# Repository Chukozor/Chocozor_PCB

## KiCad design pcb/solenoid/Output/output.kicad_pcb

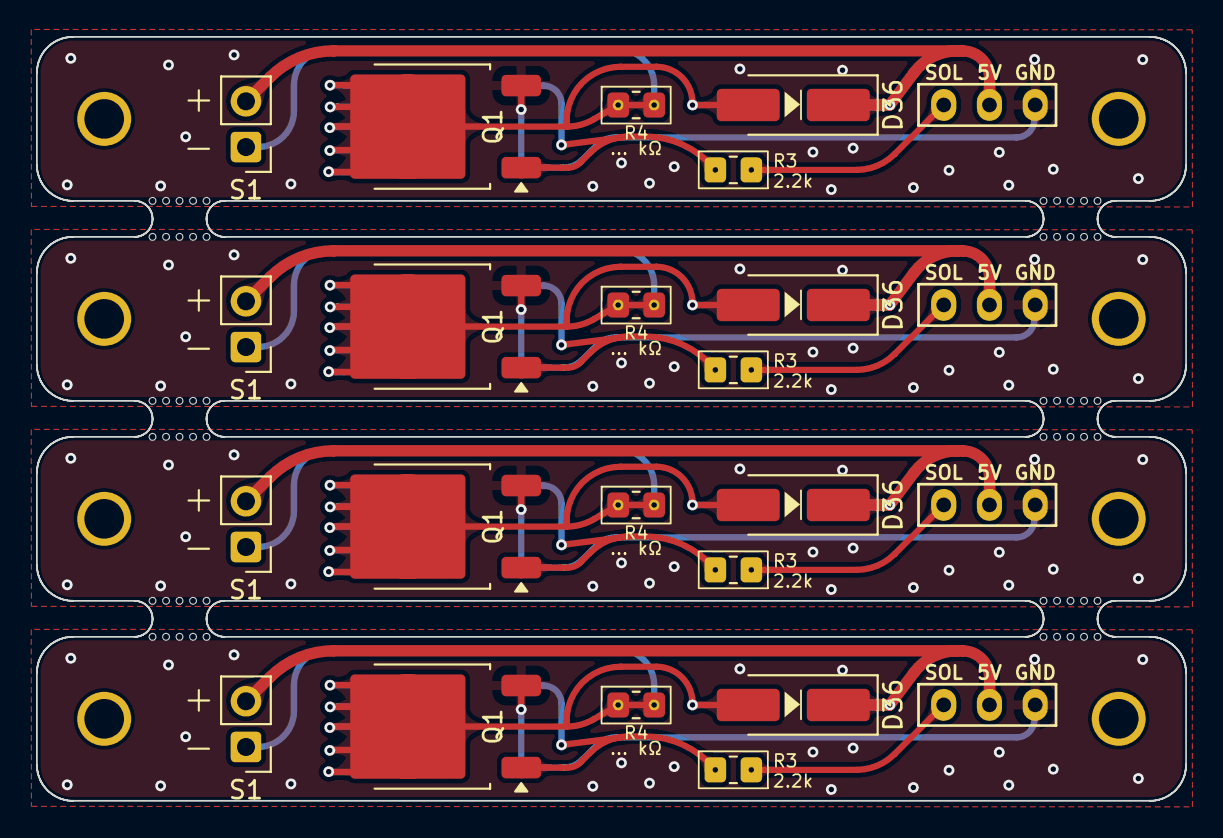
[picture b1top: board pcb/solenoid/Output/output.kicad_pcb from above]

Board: 2 copper layers, 63.8 x 42.4 mm, 92 parts (0 on the bottom side), 20 nets.

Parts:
D36, D36#2, D36#3, D36#4: SS14 (or M1) package SMA; D_SMA_Handsoldering-Chuk
J3, J3#2, J3#3, J3#4: Conn_01x03; solenoid_ribon_connector
KiKit_MB_1_1, KiKit_MB_1_2, KiKit_MB_1_3, KiKit_MB_1_4, KiKit_MB_1_5, KiKit_MB_2_1, KiKit_MB_2_2, KiKit_MB_2_3, KiKit_MB_2_4, KiKit_MB_2_5, KiKit_MB_3_1, KiKit_MB_3_2, KiKit_MB_3_3, KiKit_MB_3_4, KiKit_MB_3_5, KiKit_MB_4_1, KiKit_MB_4_2, KiKit_MB_4_3, KiKit_MB_4_4, KiKit_MB_4_5, KiKit_MB_5_1, KiKit_MB_5_2, KiKit_MB_5_3, KiKit_MB_5_4, KiKit_MB_5_5, KiKit_MB_6_1, KiKit_MB_6_2, KiKit_MB_6_3, KiKit_MB_6_4, KiKit_MB_6_5, KiKit_MB_7_1, KiKit_MB_7_2, KiKit_MB_7_3, KiKit_MB_7_4, KiKit_MB_7_5, KiKit_MB_8_1, KiKit_MB_8_2, KiKit_MB_8_3, KiKit_MB_8_4, KiKit_MB_8_5, KiKit_MB_9_1, KiKit_MB_9_2, KiKit_MB_9_3, KiKit_MB_9_4, KiKit_MB_9_5, KiKit_MB_10_1, KiKit_MB_10_2, KiKit_MB_10_3, KiKit_MB_10_4, KiKit_MB_10_5, KiKit_MB_11_1, KiKit_MB_11_2, KiKit_MB_11_3, KiKit_MB_11_4, KiKit_MB_11_5, KiKit_MB_12_1, KiKit_MB_12_2, KiKit_MB_12_3, KiKit_MB_12_4, KiKit_MB_12_5: NPTH
M2-2, M2-2#2, M2-2#3, M2-2#4, M2-3, M2-3#2, M2-3#3, M2-3#4: MountingHoleM2; Mounting-hole-M2
Q1, Q1#2, Q1#3, Q1#4: TIP120; TO-252-2-reversible
R3, R3#2, R3#3, R3#4: 2.2k; R_0805_double_face_Chukozor
R4, R4#2, R4#3, R4#4: ... kΩ; R_0805_double_face_Chukozor-Optional
S1, S1#2, S1#3, S1#4: Solenoid-PinHeader_1x02_P2.54mm_Vertical-Chuk

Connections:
Board_0-GND_Solenoid_side: J3#2.1, Q1.3 (E)
Board_0-Net-(D36-A): D36#2.2 (A), Q1.2 (C), R4#4.1, R4#4.2, S1#2.1 (GND)
Board_0-Net-(Q1-B): Q1.1 (B), R3#4.2
Board_0-SolenoidPin_Solenoid_side: J3#2.3, R3#4.1
Board_0-VBUS_Solenoid_side: D36#2.1 (K), J3#2.2, S1#2.2 (5V)
Board_1-GND_Solenoid_side: J3.1, Q1#2.3 (E)
Board_1-Net-(D36-A): D36#4.2 (A), Q1#2.2 (C), R4.1, R4.2, S1#3.1 (GND)
Board_1-Net-(Q1-B): Q1#2.1 (B), R3.2
Board_1-SolenoidPin_Solenoid_side: J3.3, R3.1
Board_1-VBUS_Solenoid_side: D36#4.1 (K), J3.2, S1#3.2 (5V)
Board_2-GND_Solenoid_side: J3#4.1, Q1#4.3 (E)
Board_2-Net-(D36-A): D36.2 (A), Q1#4.2 (C), R4#2.1, R4#2.2, S1.1 (GND)
Board_2-Net-(Q1-B): Q1#4.1 (B), R3#2.2
Board_2-SolenoidPin_Solenoid_side: J3#4.3, R3#2.1
Board_2-VBUS_Solenoid_side: D36.1 (K), J3#4.2, S1.2 (5V)
Board_3-GND_Solenoid_side: J3#3.1, Q1#3.3 (E)
Board_3-Net-(D36-A): D36#3.2 (A), Q1#3.2 (C), R4#3.1, R4#3.2, S1#4.1 (GND)
Board_3-Net-(Q1-B): Q1#3.1 (B), R3#3.2
Board_3-SolenoidPin_Solenoid_side: J3#3.3, R3#3.1
Board_3-VBUS_Solenoid_side: D36#3.1 (K), J3#3.2, S1#4.2 (5V)

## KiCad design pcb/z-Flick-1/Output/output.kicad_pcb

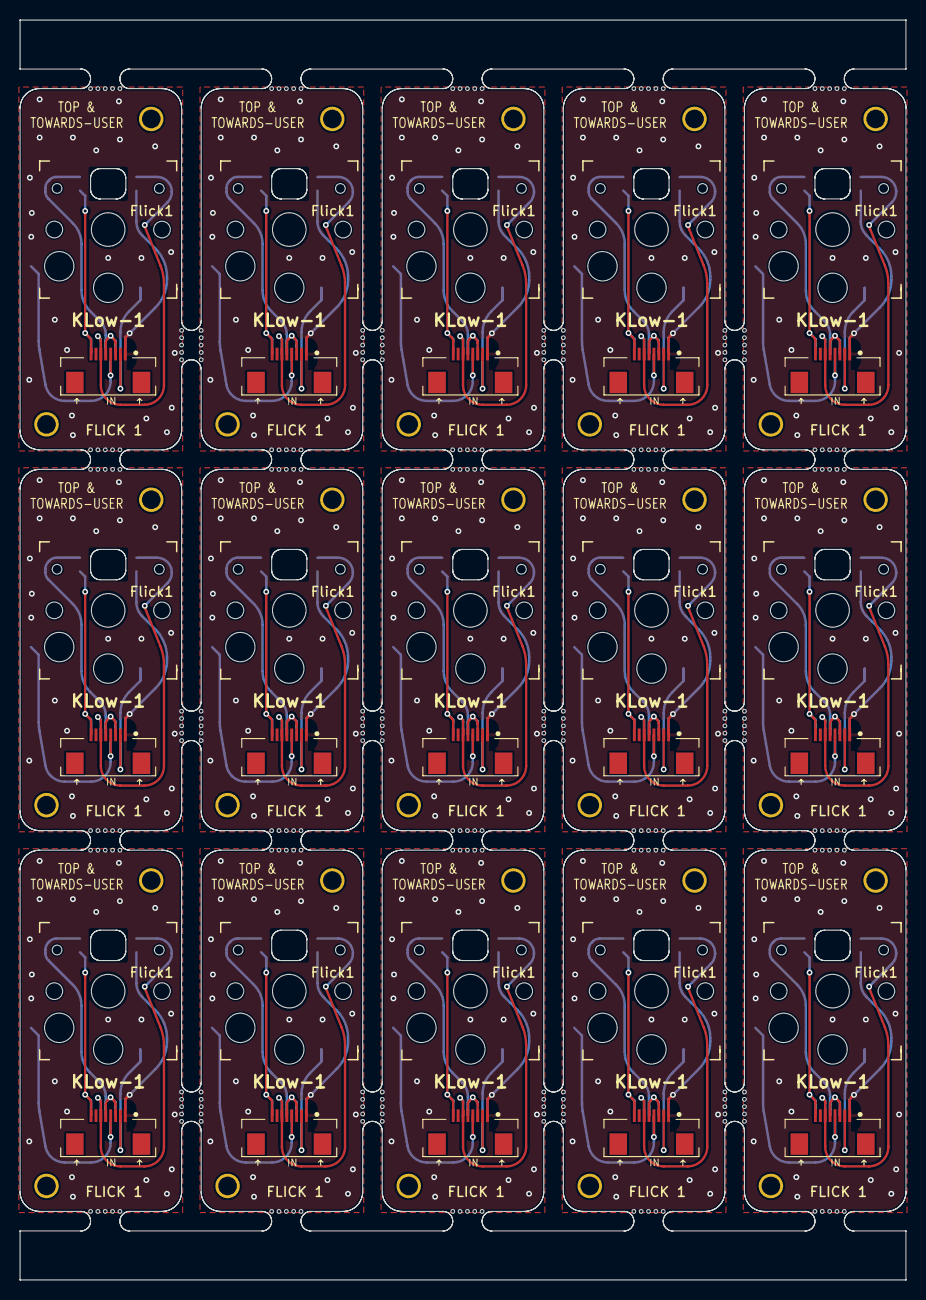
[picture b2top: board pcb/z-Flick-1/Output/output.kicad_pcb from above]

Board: 2 copper layers, 90.5 x 128.7 mm, 330 parts (0 on the bottom side), 90 nets.

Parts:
Flick1, Flick1#2, Flick1#3, Flick1#4, Flick1#5, Flick1#6, Flick1#7, Flick1#8, Flick1#9, Flick1#10, Flick1#11, Flick1#12, Flick1#13, Flick1#14, Flick1#15: SW_Chuk; Kailh_socket_PG1350_reversible_Chukozor_LED_F-MOBILE
KLow-1, KLow-1#2, KLow-1#3, KLow-1#4, KLow-1#5, KLow-1#6, KLow-1#7, KLow-1#8, KLow-1#9, KLow-1#10, KLow-1#11, KLow-1#12, KLow-1#13, KLow-1#14, KLow-1#15: FPC_8pins_687108183722; FPC_8pins_687108183722_reversible-Mobile-IN-LOW-FROMBELOW_S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
KiKit_MB_1_1, KiKit_MB_1_2, KiKit_MB_1_3, KiKit_MB_1_4, KiKit_MB_1_5, KiKit_MB_2_1, KiKit_MB_2_2, KiKit_MB_2_3, KiKit_MB_2_4, KiKit_MB_2_5, KiKit_MB_3_1, KiKit_MB_3_2, KiKit_MB_3_3, KiKit_MB_3_4, KiKit_MB_3_5, KiKit_MB_4_1, KiKit_MB_4_2, KiKit_MB_4_3, KiKit_MB_4_4, KiKit_MB_4_5, KiKit_MB_5_1, KiKit_MB_5_2, KiKit_MB_5_3, KiKit_MB_5_4, KiKit_MB_5_5, KiKit_MB_6_1, KiKit_MB_6_2, KiKit_MB_6_3, KiKit_MB_6_4, KiKit_MB_6_5, KiKit_MB_7_1, KiKit_MB_7_2, KiKit_MB_7_3, KiKit_MB_7_4, KiKit_MB_7_5, KiKit_MB_8_1, KiKit_MB_8_2, KiKit_MB_8_3, KiKit_MB_8_4, KiKit_MB_8_5, KiKit_MB_9_1, KiKit_MB_9_2, KiKit_MB_9_3, KiKit_MB_9_4, KiKit_MB_9_5, KiKit_MB_10_1, KiKit_MB_10_2, KiKit_MB_10_3, KiKit_MB_10_4, KiKit_MB_10_5, KiKit_MB_11_1, KiKit_MB_11_2, KiKit_MB_11_3, KiKit_MB_11_4, KiKit_MB_11_5, KiKit_MB_12_1, KiKit_MB_12_2, KiKit_MB_12_3, KiKit_MB_12_4, KiKit_MB_12_5, KiKit_MB_13_1, KiKit_MB_13_2, KiKit_MB_13_3, KiKit_MB_13_4, KiKit_MB_13_5, KiKit_MB_14_1, KiKit_MB_14_2, KiKit_MB_14_3, KiKit_MB_14_4, KiKit_MB_14_5, KiKit_MB_15_1, KiKit_MB_15_2, KiKit_MB_15_3, KiKit_MB_15_4, KiKit_MB_15_5, KiKit_MB_16_1, KiKit_MB_16_2, KiKit_MB_16_3, KiKit_MB_16_4, KiKit_MB_16_5, KiKit_MB_17_1, KiKit_MB_17_2, KiKit_MB_17_3, KiKit_MB_17_4, KiKit_MB_17_5, KiKit_MB_18_1, KiKit_MB_18_2, KiKit_MB_18_3, KiKit_MB_18_4, KiKit_MB_18_5, KiKit_MB_19_1, KiKit_MB_19_2, KiKit_MB_19_3, KiKit_MB_19_4, KiKit_MB_19_5, KiKit_MB_20_1, KiKit_MB_20_2, KiKit_MB_20_3, KiKit_MB_20_4, KiKit_MB_20_5, KiKit_MB_21_1, KiKit_MB_21_2, KiKit_MB_21_3, KiKit_MB_21_4, KiKit_MB_21_5, KiKit_MB_22_1, KiKit_MB_22_2, KiKit_MB_22_3, KiKit_MB_22_4, KiKit_MB_22_5, KiKit_MB_23_1, KiKit_MB_23_2, KiKit_MB_23_3, KiKit_MB_23_4, KiKit_MB_23_5, KiKit_MB_24_1, KiKit_MB_24_2, KiKit_MB_24_3, KiKit_MB_24_4, KiKit_MB_24_5, KiKit_MB_25_1, KiKit_MB_25_2, KiKit_MB_25_3, KiKit_MB_25_4, KiKit_MB_25_5, KiKit_MB_26_1, KiKit_MB_26_2, KiKit_MB_26_3, KiKit_MB_26_4, KiKit_MB_26_5, KiKit_MB_27_1, KiKit_MB_27_2, KiKit_MB_27_3, KiKit_MB_27_4, KiKit_MB_27_5, KiKit_MB_28_1, KiKit_MB_28_2, KiKit_MB_28_3, KiKit_MB_28_4, KiKit_MB_28_5, KiKit_MB_29_1, KiKit_MB_29_2, KiKit_MB_29_3, KiKit_MB_29_4, KiKit_MB_29_5, KiKit_MB_30_1, KiKit_MB_30_2, KiKit_MB_30_3, KiKit_MB_30_4, KiKit_MB_30_5, KiKit_MB_31_1, KiKit_MB_31_2, KiKit_MB_31_3, KiKit_MB_31_4, KiKit_MB_31_5, KiKit_MB_32_1, KiKit_MB_32_2, KiKit_MB_32_3, KiKit_MB_32_4, KiKit_MB_32_5, KiKit_MB_33_1, KiKit_MB_33_2, KiKit_MB_33_3, KiKit_MB_33_4, KiKit_MB_33_5, KiKit_MB_34_1, KiKit_MB_34_2, KiKit_MB_34_3, KiKit_MB_34_4, KiKit_MB_34_5, KiKit_MB_35_1, KiKit_MB_35_2, KiKit_MB_35_3, KiKit_MB_35_4, KiKit_MB_35_5, KiKit_MB_36_1, KiKit_MB_36_2, KiKit_MB_36_3, KiKit_MB_36_4, KiKit_MB_36_5, KiKit_MB_37_1, KiKit_MB_37_2, KiKit_MB_37_3, KiKit_MB_37_4, KiKit_MB_37_5, KiKit_MB_38_1, KiKit_MB_38_2, KiKit_MB_38_3, KiKit_MB_38_4, KiKit_MB_38_5, KiKit_MB_39_1, KiKit_MB_39_2, KiKit_MB_39_3, KiKit_MB_39_4, KiKit_MB_39_5, KiKit_MB_40_1, KiKit_MB_40_2, KiKit_MB_40_3, KiKit_MB_40_4, KiKit_MB_40_5, KiKit_MB_41_1, KiKit_MB_41_2, KiKit_MB_41_3, KiKit_MB_41_4, KiKit_MB_41_5, KiKit_MB_42_1, KiKit_MB_42_2, KiKit_MB_42_3, KiKit_MB_42_4, KiKit_MB_42_5, KiKit_MB_43_1, KiKit_MB_43_2, KiKit_MB_43_3, KiKit_MB_43_4, KiKit_MB_43_5, KiKit_MB_44_1, KiKit_MB_44_2, KiKit_MB_44_3, KiKit_MB_44_4, KiKit_MB_44_5, KiKit_MB_45_1, KiKit_MB_45_2, KiKit_MB_45_3, KiKit_MB_45_4, KiKit_MB_45_5, KiKit_MB_46_1, KiKit_MB_46_2, KiKit_MB_46_3, KiKit_MB_46_4, KiKit_MB_46_5, KiKit_MB_47_1, KiKit_MB_47_2, KiKit_MB_47_3, KiKit_MB_47_4, KiKit_MB_47_5, KiKit_MB_48_1, KiKit_MB_48_2, KiKit_MB_48_3, KiKit_MB_48_4, KiKit_MB_48_5, KiKit_MB_49_1, KiKit_MB_49_2, KiKit_MB_49_3, KiKit_MB_49_4, KiKit_MB_49_5, KiKit_MB_50_1, KiKit_MB_50_2, KiKit_MB_50_3, KiKit_MB_50_4, KiKit_MB_50_5, KiKit_MB_51_1, KiKit_MB_51_2, KiKit_MB_51_3, KiKit_MB_51_4, KiKit_MB_51_5, KiKit_MB_52_1, KiKit_MB_52_2, KiKit_MB_52_3, KiKit_MB_52_4, KiKit_MB_52_5, KiKit_MB_53_1, KiKit_MB_53_2, KiKit_MB_53_3, KiKit_MB_53_4, KiKit_MB_53_5, KiKit_MB_54_1, KiKit_MB_54_2, KiKit_MB_54_3, KiKit_MB_54_4, KiKit_MB_54_5: NPTH
M1.6-3, M1.6-3#2, M1.6-3#3, M1.6-3#4, M1.6-3#5, M1.6-3#6, M1.6-3#7, M1.6-3#8, M1.6-3#9, M1.6-3#10, M1.6-3#11, M1.6-3#12, M1.6-3#13, M1.6-3#14, M1.6-3#15, M1.6-4, M1.6-4#2, M1.6-4#3, M1.6-4#4, M1.6-4#5, M1.6-4#6, M1.6-4#7, M1.6-4#8, M1.6-4#9, M1.6-4#10, M1.6-4#11, M1.6-4#12, M1.6-4#13, M1.6-4#14, M1.6-4#15: MountingHoleM1.6; Mounting-hole-M1.6

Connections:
Board_0-GND_mobile_Flick1: Flick1#13.5 (VSS), KLow-1#13.6 (GND)
Board_0-Net-(Flick1-DIN): Flick1#13.6 (DIN), KLow-1#13.3 (LED->)
Board_0-Net-(Flick1-DOUT): Flick1#13.4 (DOUT), KLow-1#13.4 (LED<-)
Board_0-Net-(Flick1-VDD): Flick1#13.3 (VDD), KLow-1#13.5 (VBUS)
Board_0-Net-(KLow-1-Col2Switch): Flick1#13.1, KLow-1#13.2 (Col2Switch)
Board_0-Net-(KLow-1-Diode2Switch): Flick1#13.2, KLow-1#13.1 (Diode2Switch)
Board_1-GND_mobile_Flick1: Flick1#5.5 (VSS), KLow-1#9.6 (GND)
Board_1-Net-(Flick1-DIN): Flick1#5.6 (DIN), KLow-1#9.3 (LED->)
Board_1-Net-(Flick1-DOUT): Flick1#5.4 (DOUT), KLow-1#9.4 (LED<-)
Board_1-Net-(Flick1-VDD): Flick1#5.3 (VDD), KLow-1#9.5 (VBUS)
Board_1-Net-(KLow-1-Col2Switch): Flick1#5.1, KLow-1#9.2 (Col2Switch)
Board_1-Net-(KLow-1-Diode2Switch): Flick1#5.2, KLow-1#9.1 (Diode2Switch)
Board_2-GND_mobile_Flick1: Flick1#6.5 (VSS), KLow-1#4.6 (GND)
Board_2-Net-(Flick1-DIN): Flick1#6.6 (DIN), KLow-1#4.3 (LED->)
Board_2-Net-(Flick1-DOUT): Flick1#6.4 (DOUT), KLow-1#4.4 (LED<-)
Board_2-Net-(Flick1-VDD): Flick1#6.3 (VDD), KLow-1#4.5 (VBUS)
Board_2-Net-(KLow-1-Col2Switch): Flick1#6.1, KLow-1#4.2 (Col2Switch)
Board_2-Net-(KLow-1-Diode2Switch): Flick1#6.2, KLow-1#4.1 (Diode2Switch)
Board_3-GND_mobile_Flick1: Flick1#2.5 (VSS), KLow-1#15.6 (GND)
Board_3-Net-(Flick1-DIN): Flick1#2.6 (DIN), KLow-1#15.3 (LED->)
Board_3-Net-(Flick1-DOUT): Flick1#2.4 (DOUT), KLow-1#15.4 (LED<-)
Board_3-Net-(Flick1-VDD): Flick1#2.3 (VDD), KLow-1#15.5 (VBUS)
Board_3-Net-(KLow-1-Col2Switch): Flick1#2.1, KLow-1#15.2 (Col2Switch)
Board_3-Net-(KLow-1-Diode2Switch): Flick1#2.2, KLow-1#15.1 (Diode2Switch)
Board_4-GND_mobile_Flick1: Flick1#14.5 (VSS), KLow-1#11.6 (GND)
Board_4-Net-(Flick1-DIN): Flick1#14.6 (DIN), KLow-1#11.3 (LED->)
Board_4-Net-(Flick1-DOUT): Flick1#14.4 (DOUT), KLow-1#11.4 (LED<-)
Board_4-Net-(Flick1-VDD): Flick1#14.3 (VDD), KLow-1#11.5 (VBUS)
Board_4-Net-(KLow-1-Col2Switch): Flick1#14.1, KLow-1#11.2 (Col2Switch)
Board_4-Net-(KLow-1-Diode2Switch): Flick1#14.2, KLow-1#11.1 (Diode2Switch)
Board_5-GND_mobile_Flick1: Flick1#4.5 (VSS), KLow-1#3.6 (GND)
Board_5-Net-(Flick1-DIN): Flick1#4.6 (DIN), KLow-1#3.3 (LED->)
Board_5-Net-(Flick1-DOUT): Flick1#4.4 (DOUT), KLow-1#3.4 (LED<-)
Board_5-Net-(Flick1-VDD): Flick1#4.3 (VDD), KLow-1#3.5 (VBUS)
Board_5-Net-(KLow-1-Col2Switch): Flick1#4.1, KLow-1#3.2 (Col2Switch)
Board_5-Net-(KLow-1-Diode2Switch): Flick1#4.2, KLow-1#3.1 (Diode2Switch)
Board_6-GND_mobile_Flick1: Flick1#10.5 (VSS), KLow-1.6 (GND)
Board_6-Net-(Flick1-DIN): Flick1#10.6 (DIN), KLow-1.3 (LED->)
Board_6-Net-(Flick1-DOUT): Flick1#10.4 (DOUT), KLow-1.4 (LED<-)
Board_6-Net-(Flick1-VDD): Flick1#10.3 (VDD), KLow-1.5 (VBUS)
Board_6-Net-(KLow-1-Col2Switch): Flick1#10.1, KLow-1.2 (Col2Switch)
Board_6-Net-(KLow-1-Diode2Switch): Flick1#10.2, KLow-1.1 (Diode2Switch)
Board_7-GND_mobile_Flick1: Flick1.5 (VSS), KLow-1#2.6 (GND)
Board_7-Net-(Flick1-DIN): Flick1.6 (DIN), KLow-1#2.3 (LED->)
Board_7-Net-(Flick1-DOUT): Flick1.4 (DOUT), KLow-1#2.4 (LED<-)
Board_7-Net-(Flick1-VDD): Flick1.3 (VDD), KLow-1#2.5 (VBUS)
Board_7-Net-(KLow-1-Col2Switch): Flick1.1, KLow-1#2.2 (Col2Switch)
Board_7-Net-(KLow-1-Diode2Switch): Flick1.2, KLow-1#2.1 (Diode2Switch)
Board_8-GND_mobile_Flick1: Flick1#8.5 (VSS), KLow-1#14.6 (GND)
Board_8-Net-(Flick1-DIN): Flick1#8.6 (DIN), KLow-1#14.3 (LED->)
Board_8-Net-(Flick1-DOUT): Flick1#8.4 (DOUT), KLow-1#14.4 (LED<-)
Board_8-Net-(Flick1-VDD): Flick1#8.3 (VDD), KLow-1#14.5 (VBUS)
Board_8-Net-(KLow-1-Col2Switch): Flick1#8.1, KLow-1#14.2 (Col2Switch)
Board_8-Net-(KLow-1-Diode2Switch): Flick1#8.2, KLow-1#14.1 (Diode2Switch)
Board_9-GND_mobile_Flick1: Flick1#3.5 (VSS), KLow-1#12.6 (GND)
Board_9-Net-(Flick1-DIN): Flick1#3.6 (DIN), KLow-1#12.3 (LED->)
Board_9-Net-(Flick1-DOUT): Flick1#3.4 (DOUT), KLow-1#12.4 (LED<-)
Board_9-Net-(Flick1-VDD): Flick1#3.3 (VDD), KLow-1#12.5 (VBUS)
Board_9-Net-(KLow-1-Col2Switch): Flick1#3.1, KLow-1#12.2 (Col2Switch)
Board_9-Net-(KLow-1-Diode2Switch): Flick1#3.2, KLow-1#12.1 (Diode2Switch)
Board_10-GND_mobile_Flick1: Flick1#7.5 (VSS), KLow-1#7.6 (GND)
Board_10-Net-(Flick1-DIN): Flick1#7.6 (DIN), KLow-1#7.3 (LED->)
Board_10-Net-(Flick1-DOUT): Flick1#7.4 (DOUT), KLow-1#7.4 (LED<-)
Board_10-Net-(Flick1-VDD): Flick1#7.3 (VDD), KLow-1#7.5 (VBUS)
Board_10-Net-(KLow-1-Col2Switch): Flick1#7.1, KLow-1#7.2 (Col2Switch)
Board_10-Net-(KLow-1-Diode2Switch): Flick1#7.2, KLow-1#7.1 (Diode2Switch)
Board_11-GND_mobile_Flick1: Flick1#15.5 (VSS), KLow-1#6.6 (GND)
Board_11-Net-(Flick1-DIN): Flick1#15.6 (DIN), KLow-1#6.3 (LED->)
Board_11-Net-(Flick1-DOUT): Flick1#15.4 (DOUT), KLow-1#6.4 (LED<-)
Board_11-Net-(Flick1-VDD): Flick1#15.3 (VDD), KLow-1#6.5 (VBUS)
Board_11-Net-(KLow-1-Col2Switch): Flick1#15.1, KLow-1#6.2 (Col2Switch)
Board_11-Net-(KLow-1-Diode2Switch): Flick1#15.2, KLow-1#6.1 (Diode2Switch)
Board_12-GND_mobile_Flick1: Flick1#9.5 (VSS), KLow-1#10.6 (GND)
Board_12-Net-(Flick1-DIN): Flick1#9.6 (DIN), KLow-1#10.3 (LED->)
Board_12-Net-(Flick1-DOUT): Flick1#9.4 (DOUT), KLow-1#10.4 (LED<-)
Board_12-Net-(Flick1-VDD): Flick1#9.3 (VDD), KLow-1#10.5 (VBUS)
Board_12-Net-(KLow-1-Col2Switch): Flick1#9.1, KLow-1#10.2 (Col2Switch)
Board_12-Net-(KLow-1-Diode2Switch): Flick1#9.2, KLow-1#10.1 (Diode2Switch)
Board_13-GND_mobile_Flick1: Flick1#11.5 (VSS), KLow-1#8.6 (GND)
Board_13-Net-(Flick1-DIN): Flick1#11.6 (DIN), KLow-1#8.3 (LED->)
Board_13-Net-(Flick1-DOUT): Flick1#11.4 (DOUT), KLow-1#8.4 (LED<-)
Board_13-Net-(Flick1-VDD): Flick1#11.3 (VDD), KLow-1#8.5 (VBUS)
Board_13-Net-(KLow-1-Col2Switch): Flick1#11.1, KLow-1#8.2 (Col2Switch)
Board_13-Net-(KLow-1-Diode2Switch): Flick1#11.2, KLow-1#8.1 (Diode2Switch)
Board_14-GND_mobile_Flick1: Flick1#12.5 (VSS), KLow-1#5.6 (GND)
Board_14-Net-(Flick1-DIN): Flick1#12.6 (DIN), KLow-1#5.3 (LED->)
Board_14-Net-(Flick1-DOUT): Flick1#12.4 (DOUT), KLow-1#5.4 (LED<-)
Board_14-Net-(Flick1-VDD): Flick1#12.3 (VDD), KLow-1#5.5 (VBUS)
Board_14-Net-(KLow-1-Col2Switch): Flick1#12.1, KLow-1#5.2 (Col2Switch)
Board_14-Net-(KLow-1-Diode2Switch): Flick1#12.2, KLow-1#5.1 (Diode2Switch)

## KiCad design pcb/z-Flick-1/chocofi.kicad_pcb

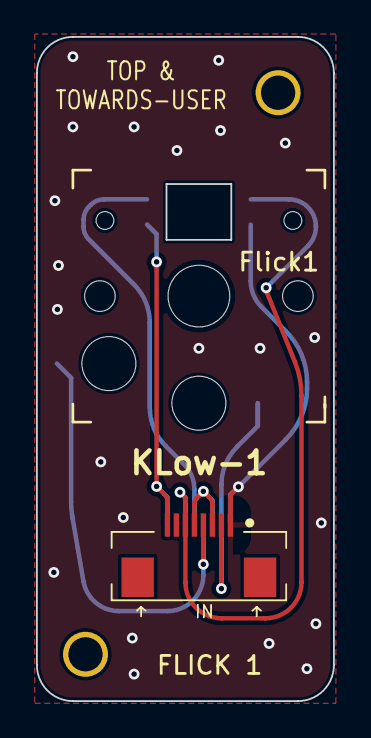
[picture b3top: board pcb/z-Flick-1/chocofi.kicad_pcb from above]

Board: 2 copper layers, 16.5 x 36.9 mm, 4 parts (0 on the bottom side), 6 nets.

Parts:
Flick1: SW_Chuk; Kailh_socket_PG1350_reversible_Chukozor_LED_F-MOBILE
KLow-1: FPC_8pins_687108183722; FPC_8pins_687108183722_reversible-Mobile-IN-LOW-FROMBELOW_S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
M1.6-3, M1.6-4: MountingHoleM1.6; Mounting-hole-M1.6

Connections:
GND_mobile_Flick1: Flick1.5 (VSS), KLow-1.6 (GND)
unnamed: Flick1.6 (DIN), KLow-1.3 (LED->)
unnamed: Flick1.4 (DOUT), KLow-1.4 (LED<-)
unnamed: Flick1.3 (VDD), KLow-1.5 (VBUS)
unnamed: Flick1.1, KLow-1.2 (Col2Switch)
unnamed: Flick1.2, KLow-1.1 (Diode2Switch)

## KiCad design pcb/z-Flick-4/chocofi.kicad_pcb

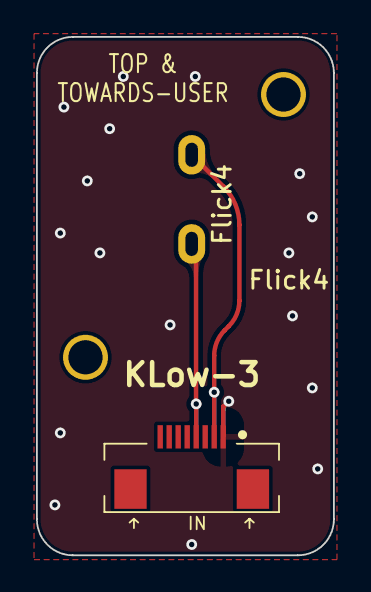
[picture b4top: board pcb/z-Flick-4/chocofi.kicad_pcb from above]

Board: 2 copper layers, 16.5 x 28.8 mm, 4 parts (0 on the bottom side), 2 nets.

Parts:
Flick4: Flick; Microswitche-2pins
KLow-3: FPC_8pins_687108183722; FPC_8pins_687108183722_reversible-Mobile-IN-LOW-FROMBELOW_S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
M1.6-13, M1.6-14: MountingHoleM1.6; Mounting-hole-M1.6

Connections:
unnamed: Flick4.1, KLow-3.2 (Col2Switch)
unnamed: Flick4.2, KLow-3.1 (Diode2Switch)
